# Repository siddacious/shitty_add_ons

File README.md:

# Artisinal Shitty Add Ons by @siddacious

* *sdo_to_quiic_qt* - to add a SAO to a SparkFunk QUIIC bus

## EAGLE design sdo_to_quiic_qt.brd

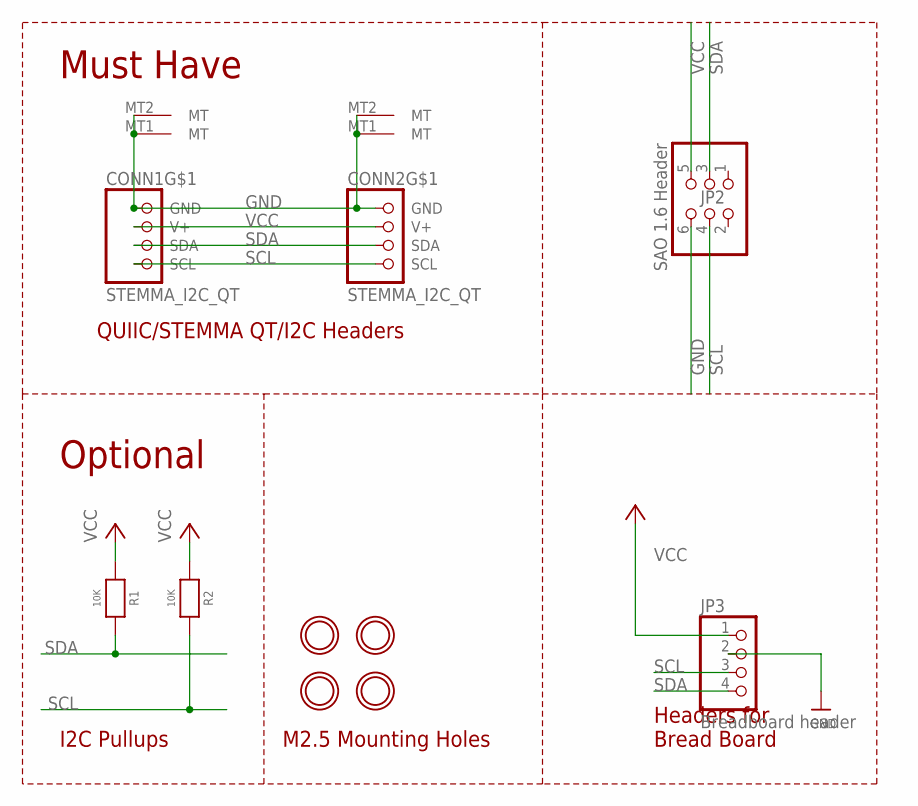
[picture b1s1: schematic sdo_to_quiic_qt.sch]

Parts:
CONN1, CONN2: STEMMA_I2C_QT; JST_SH4
JP2: SAO 1.6 Header; 2X03_ROUND_70MIL
JP3: Breadboard header; 1X04_ROUND
R1, R2: 10K; 0805-NO
U$1, U$17, U$19, U$21: MOUNTINGHOLE2.5; MOUNTINGHOLE_2.5_PLATED

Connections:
GND: CONN1.1 (GND), CONN1.MT1 (MT), CONN1.MT2 (MT), CONN2.1 (GND), CONN2.MT1 (MT), CONN2.MT2 (MT), JP2.6, JP3.2
SCL: CONN1.4 (SCL), CONN2.4 (SCL), JP2.4, JP3.3, R2.2
SDA: CONN1.3 (SDA), CONN2.3 (SDA), JP2.3, JP3.4, R1.2
VCC: CONN1.2 (V+), CONN2.2 (V+), JP2.5, JP3.1, R1.1, R2.1

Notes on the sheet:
I2C Pullups
QUIIC/STEMMA QT/I2C Headers
Headers for Bread Board
M2.5 Mounting Holes
Must Have
Optional

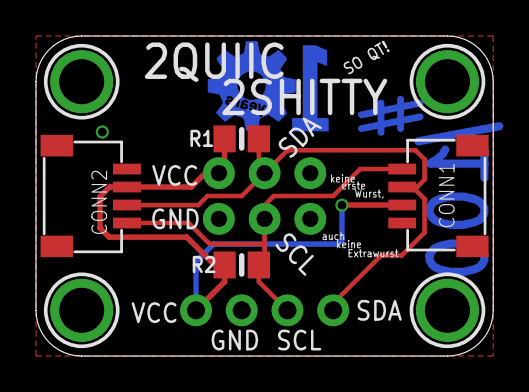
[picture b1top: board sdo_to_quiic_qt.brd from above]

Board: 2 copper layers, 25.4 x 17.8 mm, 10 parts (0 on the bottom side), 4 nets.

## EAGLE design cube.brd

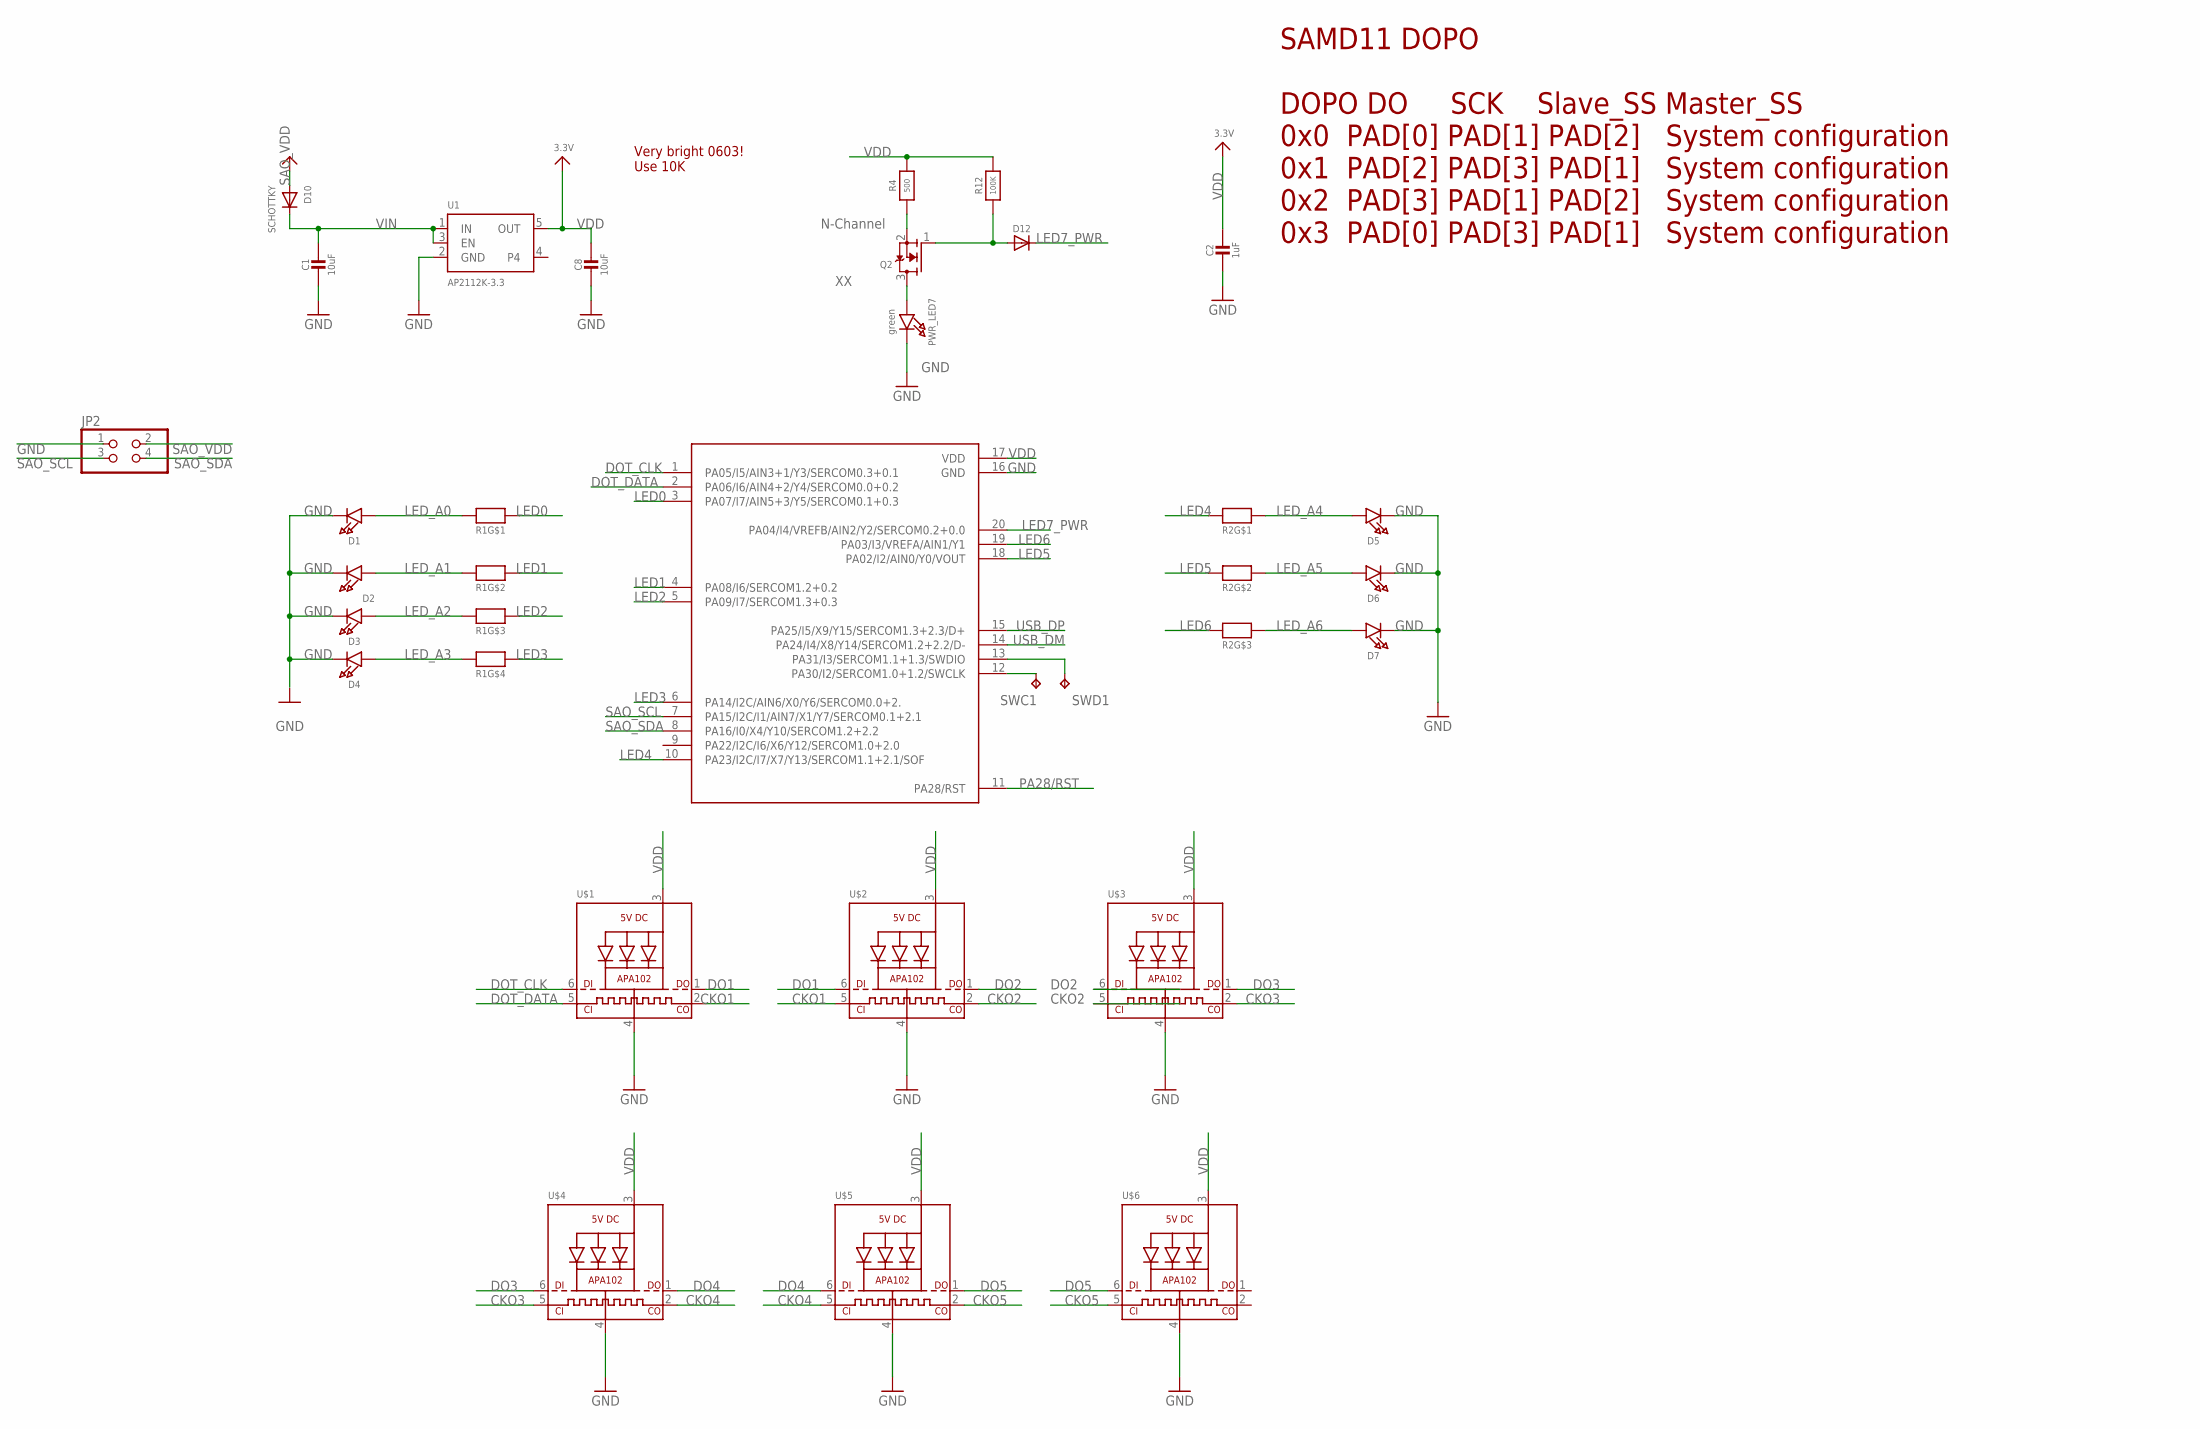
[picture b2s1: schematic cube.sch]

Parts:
C1, C8: 10uF; 0805-NO
C2: 1uF; 0603-NO
D1, D2, D3, D4, D5, D6, D7: LED0603_NOOUTLINE; CHIPLED_0603_NOOUTLINE
D10: SCHOTTKY; SOD-123FL
D12: DIODESOD-323; SOD-323
JP2: PINHD-2X2; 2X02
PWR_LED7: green; CHIPLED_0603_NOOUTLINE
Q2: MOSFET-NREFLOW; SOT23-R
R1, R2: RESISTOR_4PACK_NO; RESPACK_4X0603_NO
R4: 500; 0603-NO
R12: 100K; 0603-NO
SWC1: TPB1,27; B1,27
SWD1: TPB1,27; B1,27
U1: AP2112K-3.3; SOT23-5
U$1, U$2, U$3, U$4, U$5, U$6: APA1022020; APA102_2020
U$7: SOIC20WIDE_ATSAMD11D14A-SS; SOIC20WIDE_SOIC20WIDE

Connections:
CKO1: U$1.2 (CKO), U$2.5 (CKI)
CKO2: U$2.2 (CKO), U$3.5 (CKI)
CKO3: U$3.2 (CKO), U$4.5 (CKI)
CKO4: U$4.2 (CKO), U$5.5 (CKI)
CKO5: U$5.2 (CKO), U$6.5 (CKI)
DO1: U$1.1 (DO), U$2.6 (DI)
DO2: U$2.1 (DO), U$3.6 (DI)
DO3: U$3.1 (DO), U$4.6 (DI)
DO4: U$4.1 (DO), U$5.6 (DI)
DO5: U$5.1 (DO), U$6.6 (DI)
DOT_CLK: U$1.6 (DI), U$7.1 (PA05/I5/AIN3+1/Y3/SERCOM0.3+0.1)
DOT_DATA: U$1.5 (CKI), U$7.2 (PA06/I6/AIN4+2/Y4/SERCOM0.0+0.2)
GND: C1.2, C2.2, C8.2, D1.C, D2.C, D3.C, D4.C, D5.C, D6.C, D7.C, JP2.1, PWR_LED7.C, U1.2 (GND), U$1.4 (GND), U$2.4 (GND), U$3.4 (GND), U$4.4 (GND), U$5.4 (GND), U$6.4 (GND), U$7.16 (GND)
LED0: R1.1, U$7.3 (PA07/I7/AIN5+3/Y5/SERCOM0.1+0.3)
LED1: R1.2 (1), U$7.4 (PA08/I6/SERCOM1.2+0.2)
LED2: R1.3 (1), U$7.5 (PA09/I7/SERCOM1.3+0.3)
LED3: R1.4 (1), U$7.6 (PA14/I2C/AIN6/X0/Y6/SERCOM0.0+2.)
LED4: R2.1, U$7.10 (PA23/I2C/I7/X7/Y13/SERCOM1.1+2.1/SOF)
LED5: R2.2 (1), U$7.18 (PA02/I2/AIN0/Y0/VOUT)
LED6: R2.3 (1), U$7.19 (PA03/I3/VREFA/AIN1/Y1)
LED7_PWR: D12.C, U$7.20 (PA04/I4/VREFB/AIN2/Y2/SERCOM0.2+0.0)
LED_A0: D1.A, R1.8 (2)
LED_A1: D2.A, R1.7 (2)
LED_A2: D3.A, R1.6 (2)
LED_A3: D4.A, R1.5 (2)
LED_A4: D5.A, R2.8 (2)
LED_A5: D6.A, R2.7 (2)
LED_A6: D7.A, R2.6 (2)
unnamed: SWC1.TP, U$7.12 (PA30/I2/SERCOM1.0+1.2/SWCLK)
unnamed: D12.A, Q2.1 (G), R12.1
unnamed: SWD1.TP, U$7.13 (PA31/I3/SERCOM1.1+1.3/SWDIO)
unnamed: Q2.2 (S), R4.1
PA28/RST: U$7.11 (PA28/RST)
SAO_SCL: JP2.3, U$7.7 (PA15/I2C/I1/AIN7/X1/Y7/SERCOM0.1+2.1)
SAO_SDA: JP2.4, U$7.8 (PA16/I0/X4/Y10/SERCOM1.2+2.2)
SAO_VDD: D10.A, JP2.2
USB_DM: U$7.14 (PA24/I4/X8/Y14/SERCOM1.2+2.2/D-)
USB_DP: U$7.15 (PA25/I5/X9/Y15/SERCOM1.3+2.3/D+)
VDD: C2.1, C8.1, R4.2, R12.2, U1.5 (OUT), U$1.3 (VDD), U$2.3 (VDD), U$3.3 (VDD), U$4.3 (VDD), U$5.3 (VDD), U$6.3 (VDD), U$7.17 (VDD)
VIN: C1.1, D10.C, U1.1 (IN), U1.3 (EN)
XX: PWR_LED7.A, Q2.3 (D)

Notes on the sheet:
Very bright 0603! Use 10K
SAMD11 DOPO DOPO DO SCK Slave_SS Master_SS 0x0 PAD[0] PAD[1] PAD[2] System configuration 0x1 PAD[2] PAD[3] PAD[1] System configuration 0x2 PAD[3] PAD[1] PAD[2] System configuration 0x3 PAD[0] PAD[3] PAD[1] System configuration
N-Channel

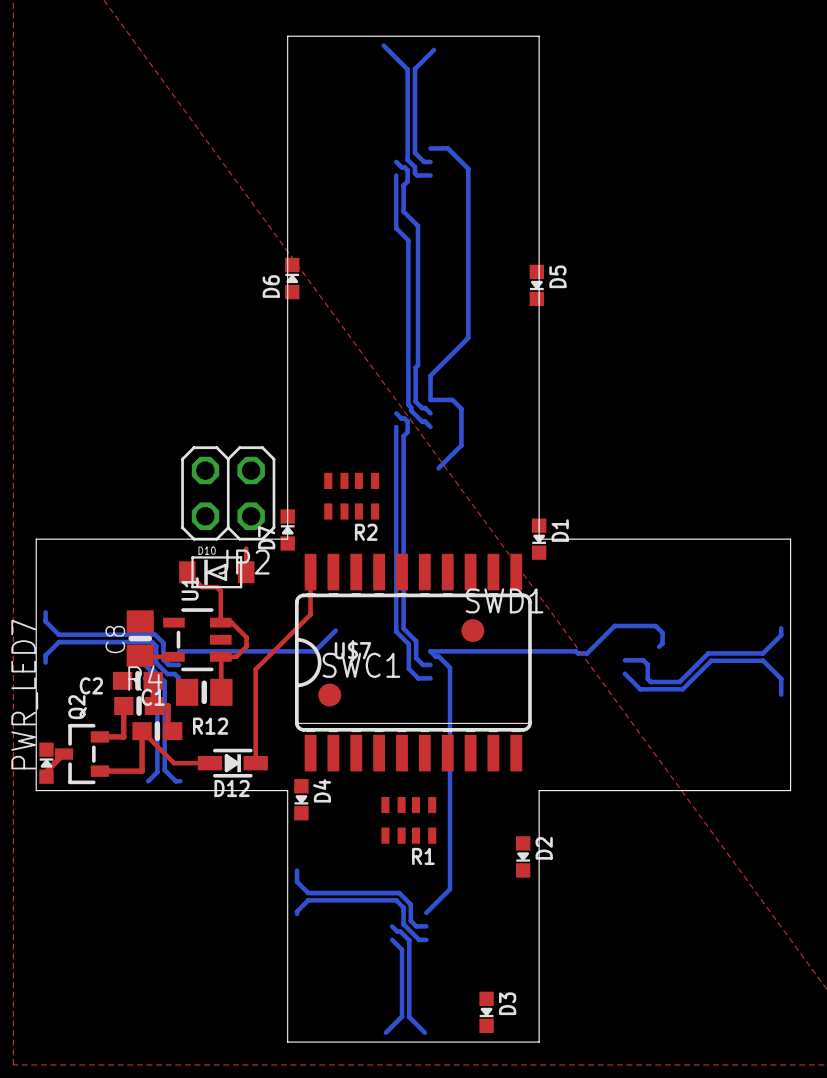
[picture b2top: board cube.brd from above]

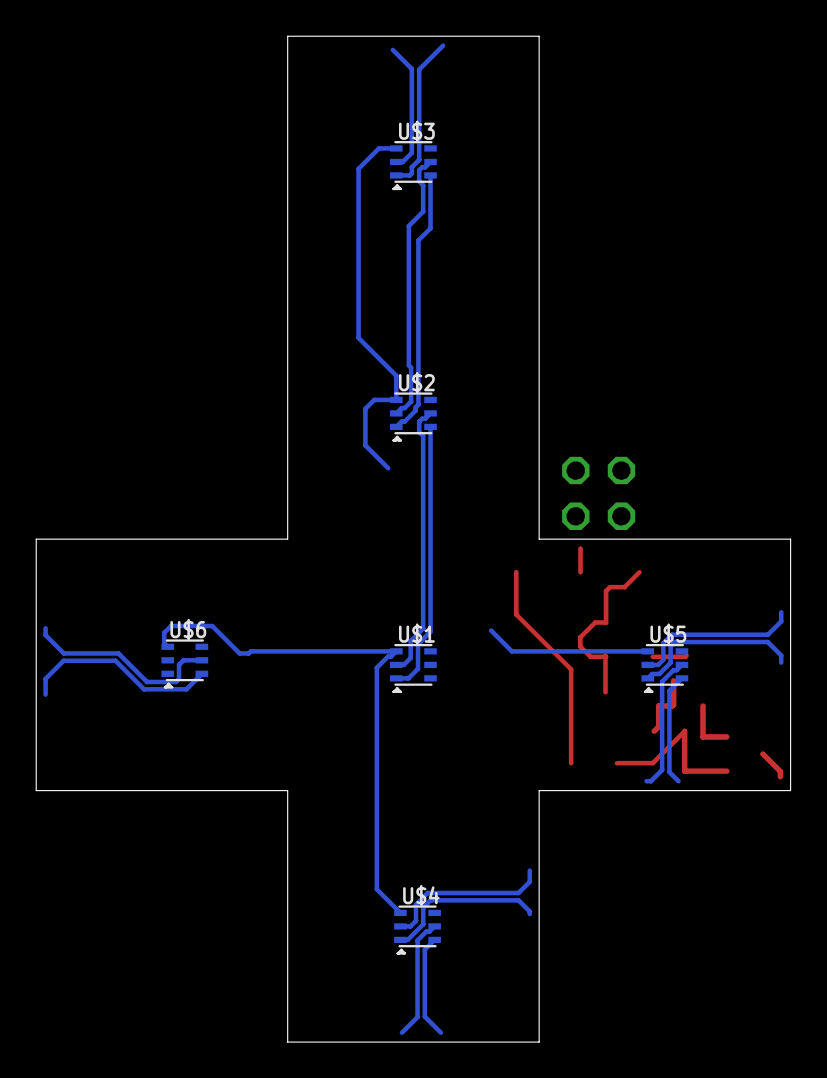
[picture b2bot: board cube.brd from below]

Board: 2 copper layers, 41.9 x 55.9 mm, 29 parts (6 on the bottom side), 38 nets.

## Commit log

2020-02-17 initial commit, not routed
2020-02-17 adding readme
2020-02-23 adding cube schem
2020-02-23 saving progress
2020-02-24 routed
2020-02-24 renamed, tweaked
2020-02-24 made LED7 also a power led
2020-02-24 updtes with suggestion from cgrover
2020-02-25 silk
2020-02-25 silk 2
2020-02-25 adding speedypoo script, updating cube
2020-02-27 cleanup
2020-02-27 resizing
2020-02-27 adjusting silks
2020-02-27 final silk?
2020-03-02 mostly there
2020-03-02 new thing
2020-03-03 near done?
2020-03-03 poo done
2020-03-03 done but for x/100
2020-03-04 progress
2020-03-04 rearranging
2020-03-04 more progress
2020-03-04 done
2020-03-04 ok, really as ordered 3Qkj6FCq

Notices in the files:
parts and their libraries:
microbuilder: This work is placed in the public domain, and may be freely used for commercial and non-commercial work with the following conditions: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
